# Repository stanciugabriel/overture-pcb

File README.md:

# Overture PCB

Overture is a custom ESP32-C6 control board designed to drive a NEMA 17 stepper motor while handling NFC reading, a small display, and physical user inputs. Everything is powered through a single USB-C Power Delivery connection.

## Hardware Specs

* **Microcontroller:** ESP32-C6-WROOM-1
* **Motor Driver:** TMC2208/TMC2209 setup driving a JST-XH port, sized for a NEMA 17 stepper.
* **Peripheral Headers:** Broken out pins for an ST7789 TFT screen, a PN532 NFC module, 3 push buttons, and a rotary encoder.
* **Power Delivery:** Uses an STUSB4500 PD controller to negotiate 20V directly from a USB-C wall adapter.
* **Power Regulation:** A TPS54308DDCT buck converter steps the 20V down to 3.3V (up to 2A max) to power the ESP32 and logic peripherals.
* **Programming:** Features a secondary USB-C port dedicated strictly to flashing and serial output.

## Power and Flashing

The board uses a dual USB-C port design to separate power and data. 

To power the motor and board, plug a compatible USB-C PD charger into the main power port. The STUSB4500 handles the 20V negotiation automatically. 

To flash the ESP32, use the secondary USB-C port. Note that the primary power port does not route data lines to the ESP32 and will not show up as a COM port on your machine.

## Exports

The exports folder contains all the file for production:
* hw1-bom.csv - is the Bill of Materials (formatted for JLCPCB)
* hw1-top-pos.csv - is the Components Position File for PCB-A (formatted for JLCPCB)
* Gerber_Archived.zip - has all the Gerber and Drill files needed for production

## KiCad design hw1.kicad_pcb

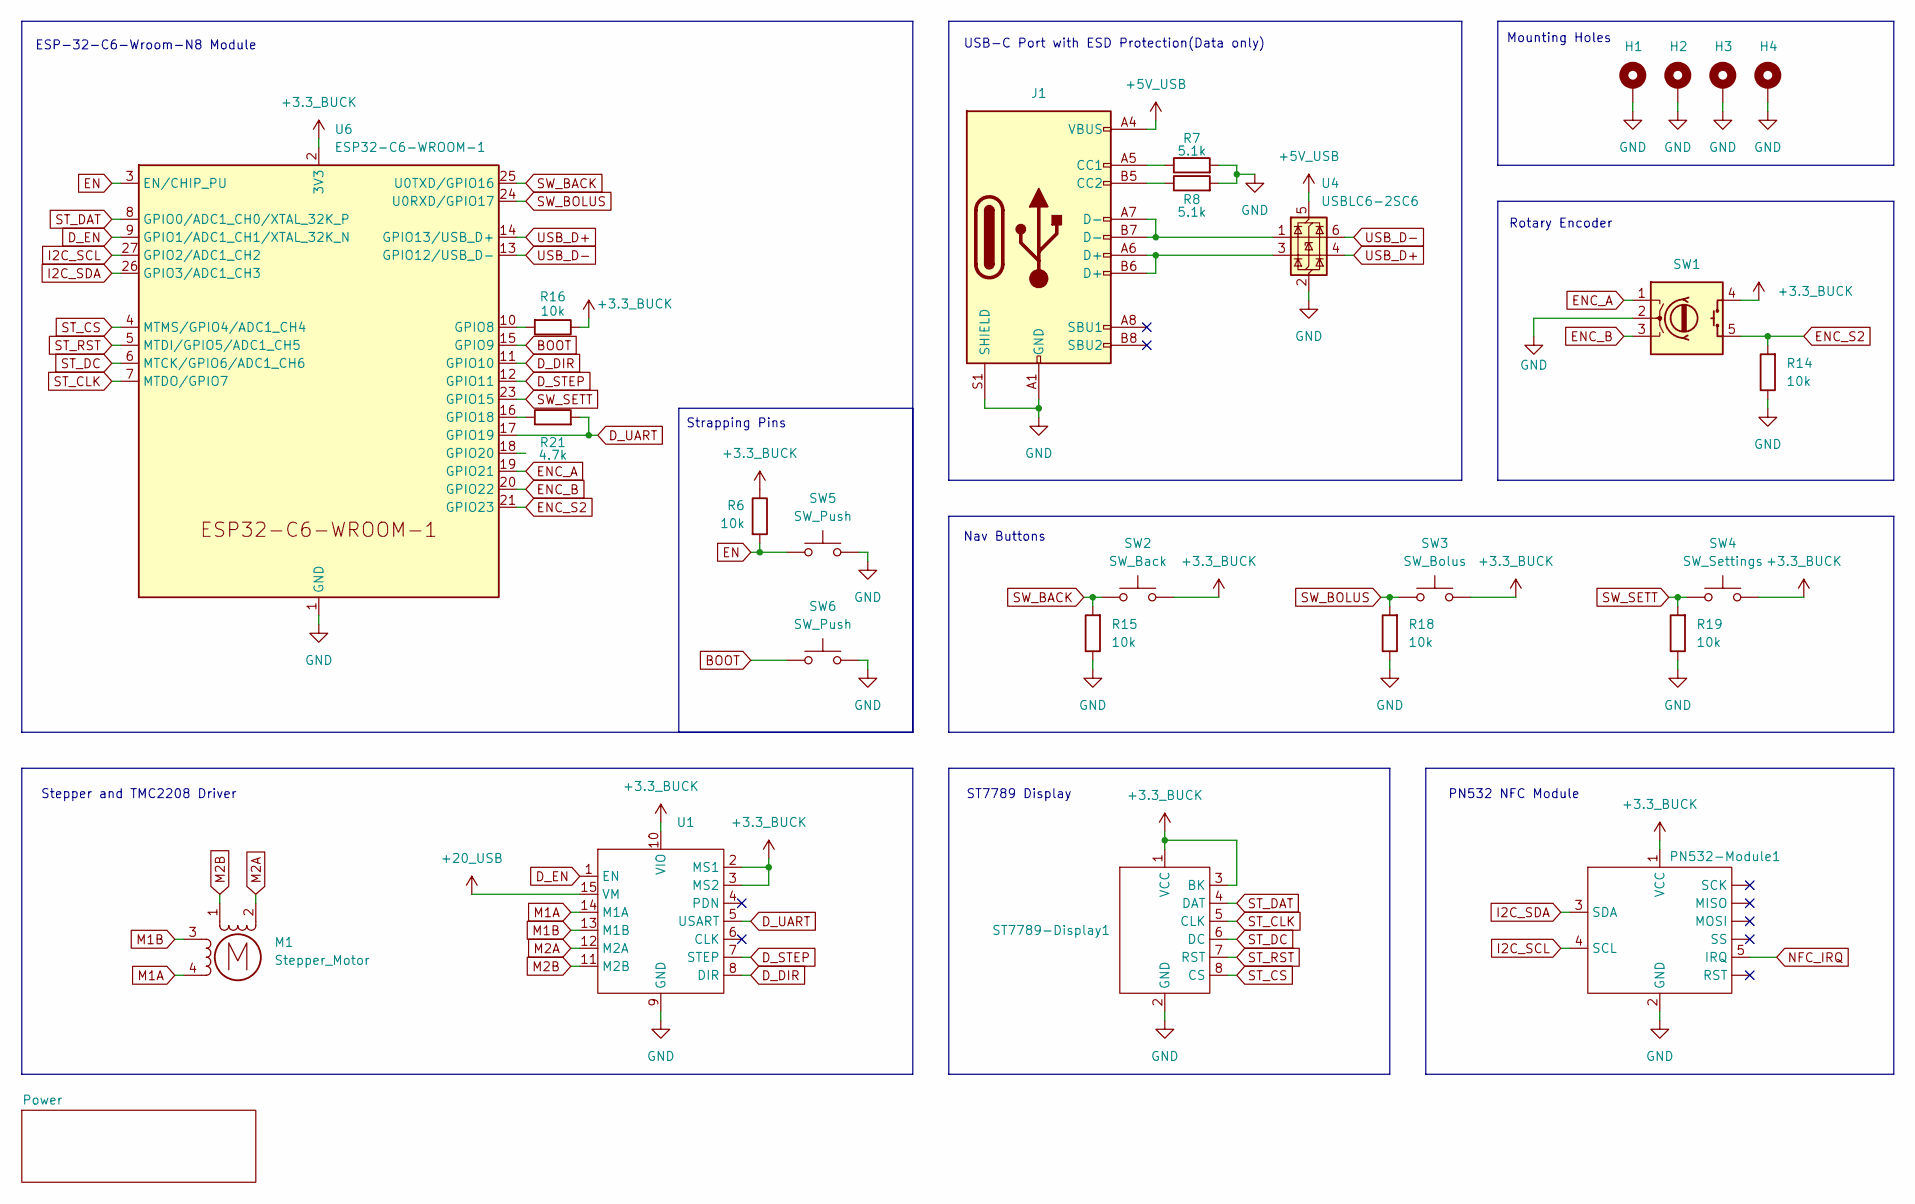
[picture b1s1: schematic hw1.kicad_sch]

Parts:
H1, H2, H3, H4: MountingHole_Pad; MountingHole_3mm_Pad_Via
J1: USB_C_Receptacle_USB2.0_16P; USB_C_Receptacle_GCT_USB4105-xx-A_16P_TopMnt_Horizontal; LCSC C2765186
M1: Stepper_Motor; JST_XH_S4B-XH-A_1x04_P2.50mm_Horizontal; LCSC C5361047
PN532-Module1: PinHeader_1x05_P2.54mm_Vertical
R6, R14, R15, R16, R18, R19: 10k; R_0603_1608Metric; LCSC C25804
R7, R8: 5.1k; R_0603_1608Metric; LCSC C23186
R21: 4.7k; R_0603_1608Metric; LCSC C23162
ST7789-Display1: PinHeader_1x08_P2.54mm_Vertical
SW1: RotaryEncoder_Switch; PinHeader_1x05_P2.54mm_Vertical
SW2: SW_Back; PinHeader_2x01_P2.54mm_Vertical
SW3: SW_Bolus; PinHeader_2x01_P2.54mm_Vertical
SW4: SW_Settings; PinHeader_2x01_P2.54mm_Vertical
SW5, SW6: SW_Push; SW_TS-1088-AR02016; LCSC C720477
U1: TMC2208_edit
U4: USBLC6-2SC6; SOT-23-6; LCSC C7519
U6: ESP32-C6-WROOM-1; ESP32-C6-WROOM-1_edit; LCSC C5366877

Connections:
+3.3_BUCK: PN532-Module1.1 (VCC), R6.1, R16.1, ST7789-Display1.1 (VCC), ST7789-Display1.3 (BK), SW1.4 (S1), SW2.2, SW3.2, SW4.2, U1.2 (MS1), U1.3 (MS2), U1.10 (VIO), U6.2 (3V3); also elsewhere on the board
+5V_USB: J1.A4 (VBUS), J1.A9 (VBUS), J1.B4 (VBUS), J1.B9 (VBUS), U4.5 (VBUS)
+20_USB: U1.15 (VM); also elsewhere on the board
BOOT: SW6.1, U6.15 (GPIO9)
D_DIR: U1.8 (DIR), U6.11 (GPIO10)
D_EN: U1.1 (EN), U6.9 (GPIO1/ADC1_CH1/XTAL_32K_N)
D_STEP: U1.7 (STEP), U6.12 (GPIO11)
D_UART: R21.2, U1.5 (USART), U6.17 (GPIO19)
EN: R6.2, SW5.1, U6.3 (EN/CHIP_PU)
ENC_A: SW1.1 (A), U6.19 (GPIO21)
ENC_B: SW1.3 (B), U6.20 (GPIO22)
ENC_S2: R14.2, SW1.5 (S2), U6.21 (GPIO23)
GND: H1.1, H2.1, H3.1, H4.1, J1.A1 (GND), J1.A12 (GND), J1.B1 (GND), J1.B12 (GND), J1.S1 (SHIELD), PN532-Module1.2 (GND), R7.2, R8.2, R14.1, R15.1, R18.1, R19.1, ST7789-Display1.2 (GND), SW1.2 (C), SW5.2, SW6.2, U1.9 (GND), U4.2 (GND), U6.1 (GND), U6.28 (GND), U6.29 (GND); also elsewhere on the board
I2C_SCL: PN532-Module1.4 (SCL), U6.27 (GPIO2/ADC1_CH2); also elsewhere on the board
I2C_SDA: PN532-Module1.3 (SDA), U6.26 (GPIO3/ADC1_CH3); also elsewhere on the board
M1A: M1.4, U1.14 (M1A)
M1B: M1.3, U1.13 (M1B)
M2A: M1.2 (-), U1.12 (M2A)
M2B: M1.1, U1.11 (M2B)
NFC_IRQ: PN532-Module1.5 (IRQ)
unnamed: J1.A5 (CC1), R7.1
unnamed: J1.B5 (CC2), R8.1
unnamed: J1.A6 (D+), J1.B6 (D+), U4.3 (I/O2)
unnamed: J1.A7 (D-), J1.B7 (D-), U4.1 (I/O1)
unnamed: R16.2, U6.10 (GPIO8)
unnamed: R21.1, U6.16 (GPIO18)
ST_CLK: ST7789-Display1.5 (CLK), U6.7 (MTDO/GPIO7)
ST_CS: ST7789-Display1.8 (CS), U6.4 (MTMS/GPIO4/ADC1_CH4)
ST_DAT: ST7789-Display1.4 (DAT), U6.8 (GPIO0/ADC1_CH0/XTAL_32K_P)
ST_DC: ST7789-Display1.6 (DC), U6.6 (MTCK/GPIO6/ADC1_CH6)
ST_RST: ST7789-Display1.7 (RST), U6.5 (MTDI/GPIO5/ADC1_CH5)
SW_BACK: R15.2, SW2.1, U6.25 (U0TXD/GPIO16)
SW_BOLUS: R18.2, SW3.1, U6.24 (U0RXD/GPIO17)
SW_SETT: R19.2, SW4.1, U6.23 (GPIO15)
USB_D+: U4.4 (I/O2), U6.14 (GPIO13/USB_D+)
USB_D-: U4.6 (I/O1), U6.13 (GPIO12/USB_D-)

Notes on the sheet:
USB-C Port with ESD Protection(Data only)
Nav Buttons
ESP-32-C6-Wroom-N8 Module
ST7789 Display
Rotary Encoder
PN532 NFC Module
Mounting Holes
Strapping Pins
Stepper and TMC2208 Driver

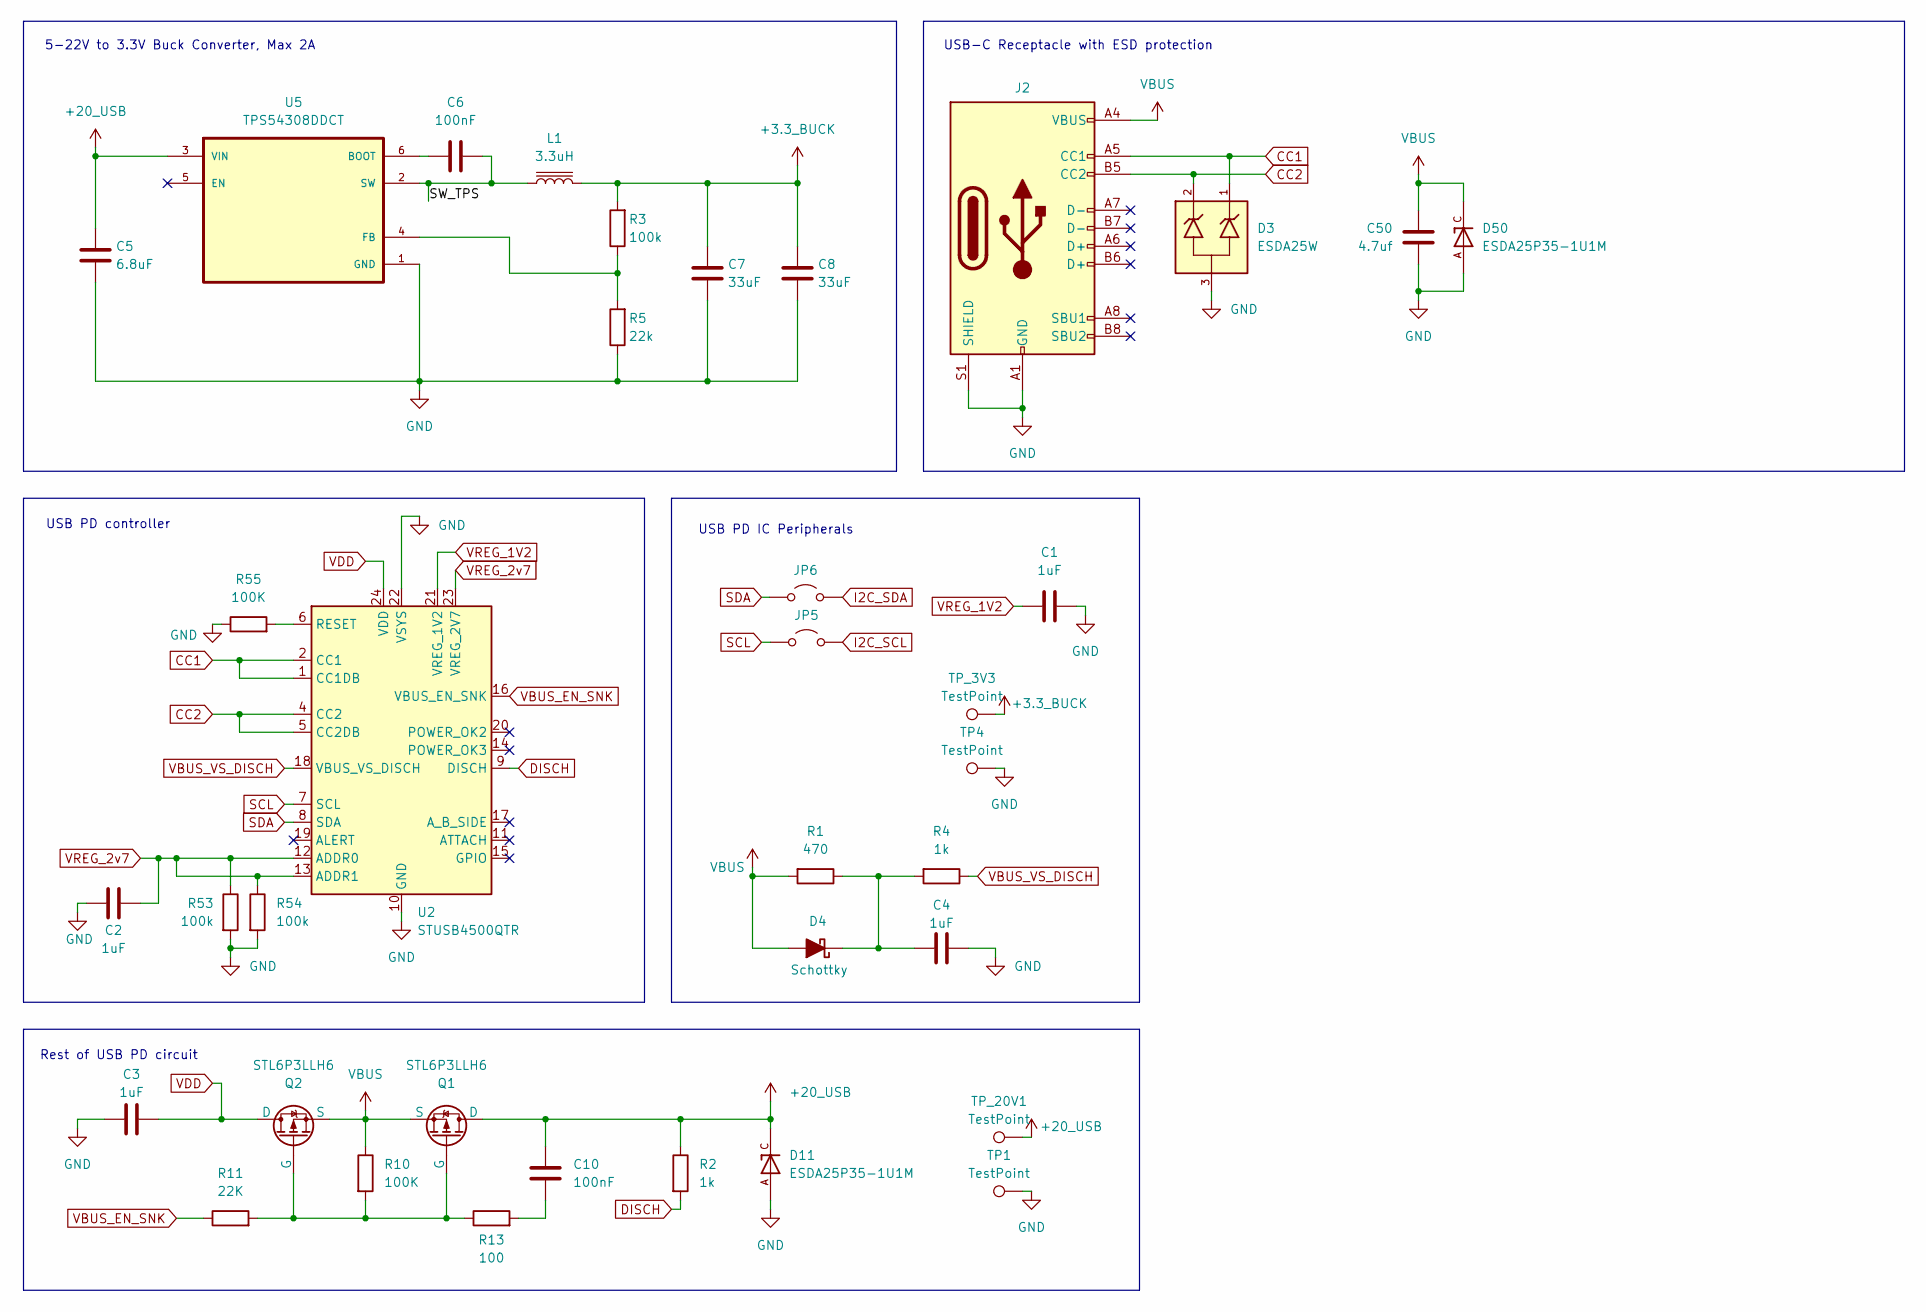
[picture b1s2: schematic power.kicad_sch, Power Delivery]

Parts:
C1, C2, C3, C4: 1uF; C_0603_1608Metric; LCSC C5199872
C5: 6.8uF; C_1206_3216Metric; LCSC C92797
C6, C10: 100nF; C_0402_1005Metric; LCSC C307331
C7, C8: 33uF; C_0805_2012Metric; LCSC C342635
C50: 4.7uf; C_1206_3216Metric; LCSC C29823
D3: ESDA25W; SOT65P210X110-3N; PARTREV 2; LCSC C2935152
D4: Schottky; D_SOD-323; LCSC C7502694
D11, D50: ESDA25P35-1U1M; TVS_ESDA25P35-1U1M; PARTREV 2; LCSC C1974707
J2: USB_C_Receptacle_USB2.0_16P; USB_C_Receptacle_GCT_USB4105-xx-A_16P_TopMnt_Horizontal; LCSC C2765186
JP5, JP6: SolderJumper-2_P1.3mm_Bridged_RoundedPad1.0x1.5mm
L1: 3.3uH; IND-SMD_L7.2-W6.6_GPSR07X0; LCSC C5189747
Q1, Q2: STL6P3LLH6; mosfetty; LCSC C49452349
R1: 470; R_0603_1608Metric; LCSC C23179
R2, R4: 1k; R_1206_3216Metric; LCSC C4410
R3: 100k; R_0402_1005Metric; LCSC C25741
R5: 22k; R_0603_1608Metric; LCSC C31850
R10, R55: 100K; R_0603_1608Metric; LCSC C25803
R11: 22K; R_0603_1608Metric; LCSC C31850
R13: 100; R_0603_1608Metric; LCSC C22775
R53, R54: 100k; R_0603_1608Metric; LCSC C25803
TP1, TP4: TestPoint; TestPoint_Pad_D3.0mm
TP_3V3, TP_20V1: TestPoint; TestPoint_Pad_D3.0mm
U2: STUSB4500QTR; QFN-24-1EP_4x4mm_P0.5mm_EP2.65x2.65mm; LCSC C2678061
U5: TPS54308DDCT; SOT95P280X110-6N; DigiKey_Part_Number 296-47881-1-ND

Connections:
+3.3_BUCK: C7.2, C8.2, L1.2, R3.2, TP_3V3.1; also elsewhere on the board
+20_USB: C5.2, C10.1, D11.C, Q1.1 (D), R2.1, TP_20V1.1, U5.3 (VIN); also elsewhere on the board
/Power/SW_TPS: C6.1, L1.1, U5.2 (SW)
CC1: D3.1, J2.A5 (CC1), U2.1 (CC1DB), U2.2 (CC1)
CC2: D3.2, J2.B5 (CC2), U2.4 (CC2), U2.5 (CC2DB)
DISCH: R2.2, U2.9 (DISCH)
GND: C1.2, C2.2, C3.1, C4.2, C5.1, C7.1, C8.1, C50.2, D3.3, D11.A, D50.A, J2.A1 (GND), J2.A12 (GND), J2.B1 (GND), J2.B12 (GND), J2.S1 (SHIELD), R5.1, R53.2, R54.2, R55.1, TP1.1, TP4.1, U2.10 (GND), U2.22 (VSYS), U2.25 (GND), U5.1 (GND); also elsewhere on the board
I2C_SCL: JP5.2 (B); also elsewhere on the board
I2C_SDA: JP6.2 (B); also elsewhere on the board
unnamed: C10.2, R13.2
unnamed: C4.1, D4.1 (K), R1.1, R4.2
unnamed: Q1.2 (G), Q2.2 (G), R10.2, R11.2, R13.1
unnamed: R55.2, U2.6 (RESET)
unnamed: C6.2, U5.6 (BOOT)
unnamed: R3.1, R5.2, U5.4 (FB)
SCL: JP5.1 (A), U2.7 (SCL)
SDA: JP6.1 (A), U2.8 (SDA)
VBUS: C50.1, D4.2 (A), D50.C, J2.A4 (VBUS), J2.A9 (VBUS), J2.B4 (VBUS), J2.B9 (VBUS), Q1.3 (S), Q2.3 (S), R1.2, R10.1
VBUS_EN_SNK: R11.1, U2.16 (VBUS_EN_SNK)
VBUS_VS_DISCH: R4.1, U2.18 (VBUS_VS_DISCH)
VDD: C3.2, Q2.1 (D), U2.24 (VDD)
VREG_1V2: C1.1, U2.21 (VREG_1V2)
VREG_2v7: C2.1, R53.1, R54.1, U2.12 (ADDR0), U2.13 (ADDR1), U2.23 (VREG_2V7)

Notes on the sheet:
USB PD controller
Rest of USB PD circuit
USB-C Receptacle with ESD protection
USB PD IC Peripherals
5-22V to 3.3V Buck Converter, Max 2A

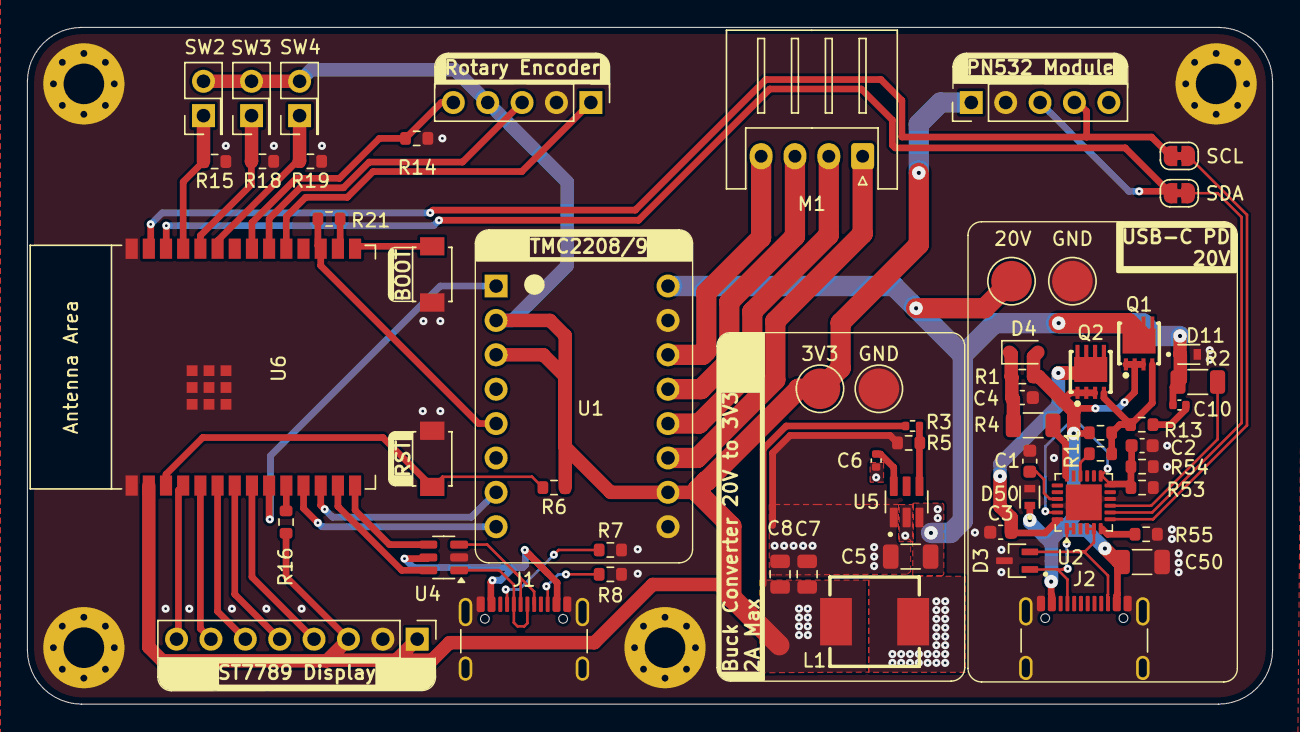
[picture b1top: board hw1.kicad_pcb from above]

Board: 2 copper layers, 92.0 x 50.0 mm, 63 parts (0 on the bottom side), 53 nets.

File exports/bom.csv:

"Id";"Designator";"Footprint";"Quantity";"Designation";"Supplier and ref";
1;"L2";"IND-SMD_L7.2-W6.6_GPSR07X0";1;"3.3uH";;;
2;"R5";"R_0603_1608Metric";1;"22k";;;
3;"D4";"D_SOD-323";1;"Schottky";;;
4;"M1";"JST_XH_S4B-XH-A_1x04_P2.50mm_Horizontal";1;"Stepper_Motor";;;
5;"R1";"R_0603_1608Metric";1;"470";;;
6;"U2";"QFN-24-1EP_4x4mm_P0.5mm_EP2.65x2.65mm";1;"STUSB4500QTR";;;
7;"R54,R53";"R_0603_1608Metric";2;"100k";;;
8;"R18,R19,R14,R15";"R_0603_1608Metric";4;"10k";;;
9;"C3,C4,C1,C2";"C_0603_1608Metric";4;"1uF";;;
10;"JP6,JP5";"SolderJumper-2_P1.3mm_Bridged_RoundedPad1.0x1.5mm";2;"~";;;
11;"C7,C8";"C_0805_2012Metric";2;"33uF";;;
12;"D3";"SOT65P210X110-3N";1;"ESDA25W";;;
13;"U4";"XIAO-RP2350-DIP";1;"XIAO-RP2350-DIP";;;
14;"R4,R2";"R_1206_3216Metric";2;"1k";;;
15;"R3";"R_0402_1005Metric";1;"100k";;;
16;"PN532-Module1";"PinHeader_1x05_P2.54mm_Vertical";1;"~";;;
17;"R55,R10";"R_0603_1608Metric";2;"100K";;;
18;"TP_20V1,TP4,TP_3V3,TP1";"TestPoint_Pad_D3.0mm";4;"TestPoint";;;
19;"C5";"C_1206_3216Metric";1;"6.8uF";;;
20;"Q1";"TRANS_STL6P3LLH6";1;"STL6P3LLH6";;;
21;"U1";"TMC2208";1;"~";;;
22;"R11";"R_0603_1608Metric";1;"22K";;;
23;"SW2";"PinHeader_2x01_P2.54mm_Vertical";1;"SW_Back";;;
24;"SW4";"PinHeader_2x01_P2.54mm_Vertical";1;"SW_Settings";;;
25;"ST7789-Display1";"PinHeader_1x08_P2.54mm_Vertical";1;"~";;;
26;"C10,C6";"C_0402_1005Metric";2;"100nF";;;
27;"SW3";"PinHeader_2x01_P2.54mm_Vertical";1;"SW_Bolus";;;
28;"SW1";"PinHeader_1x05_P2.54mm_Vertical";1;"RotaryEncoder_Switch";;;
29;"R13";"R_0603_1608Metric";1;"100";;;
30;"D50,D11";"TVS_ESDA25P35-1U1M";2;"ESDA25P35-1U1M";;;
31;"R21";"R_0603_1608Metric";1;"4.7k";;;
32;"U5";"SOT95P280X110-6N";1;"TPS54308DDCT";;;
33;"J2";"USB_C_Receptacle_HRO_TYPE-C-31-M-12";1;"USB_C_Receptacle_USB2.0_16P";;;
34;"C50";"C_1206_3216Metric";1;"4.7uf";;;

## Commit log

2026-04-17 Finalized the first version, and rearranged file structure
2026-04-17 Added thicker traces for the whole MCU part. Still need to fix some DRC errors related to the XIAO's castellated pins.
2026-04-21 Re-arranged some traces
2026-04-24 Finalized PCB design, still have to tweak some stuff though
2026-04-25 Added LCSC codes, swapped extended components for basic ones, fixed labels and tidied schematics.
2026-04-25 added readme image
2026-05-07 Finalised design, sent PCB to manufacturing
